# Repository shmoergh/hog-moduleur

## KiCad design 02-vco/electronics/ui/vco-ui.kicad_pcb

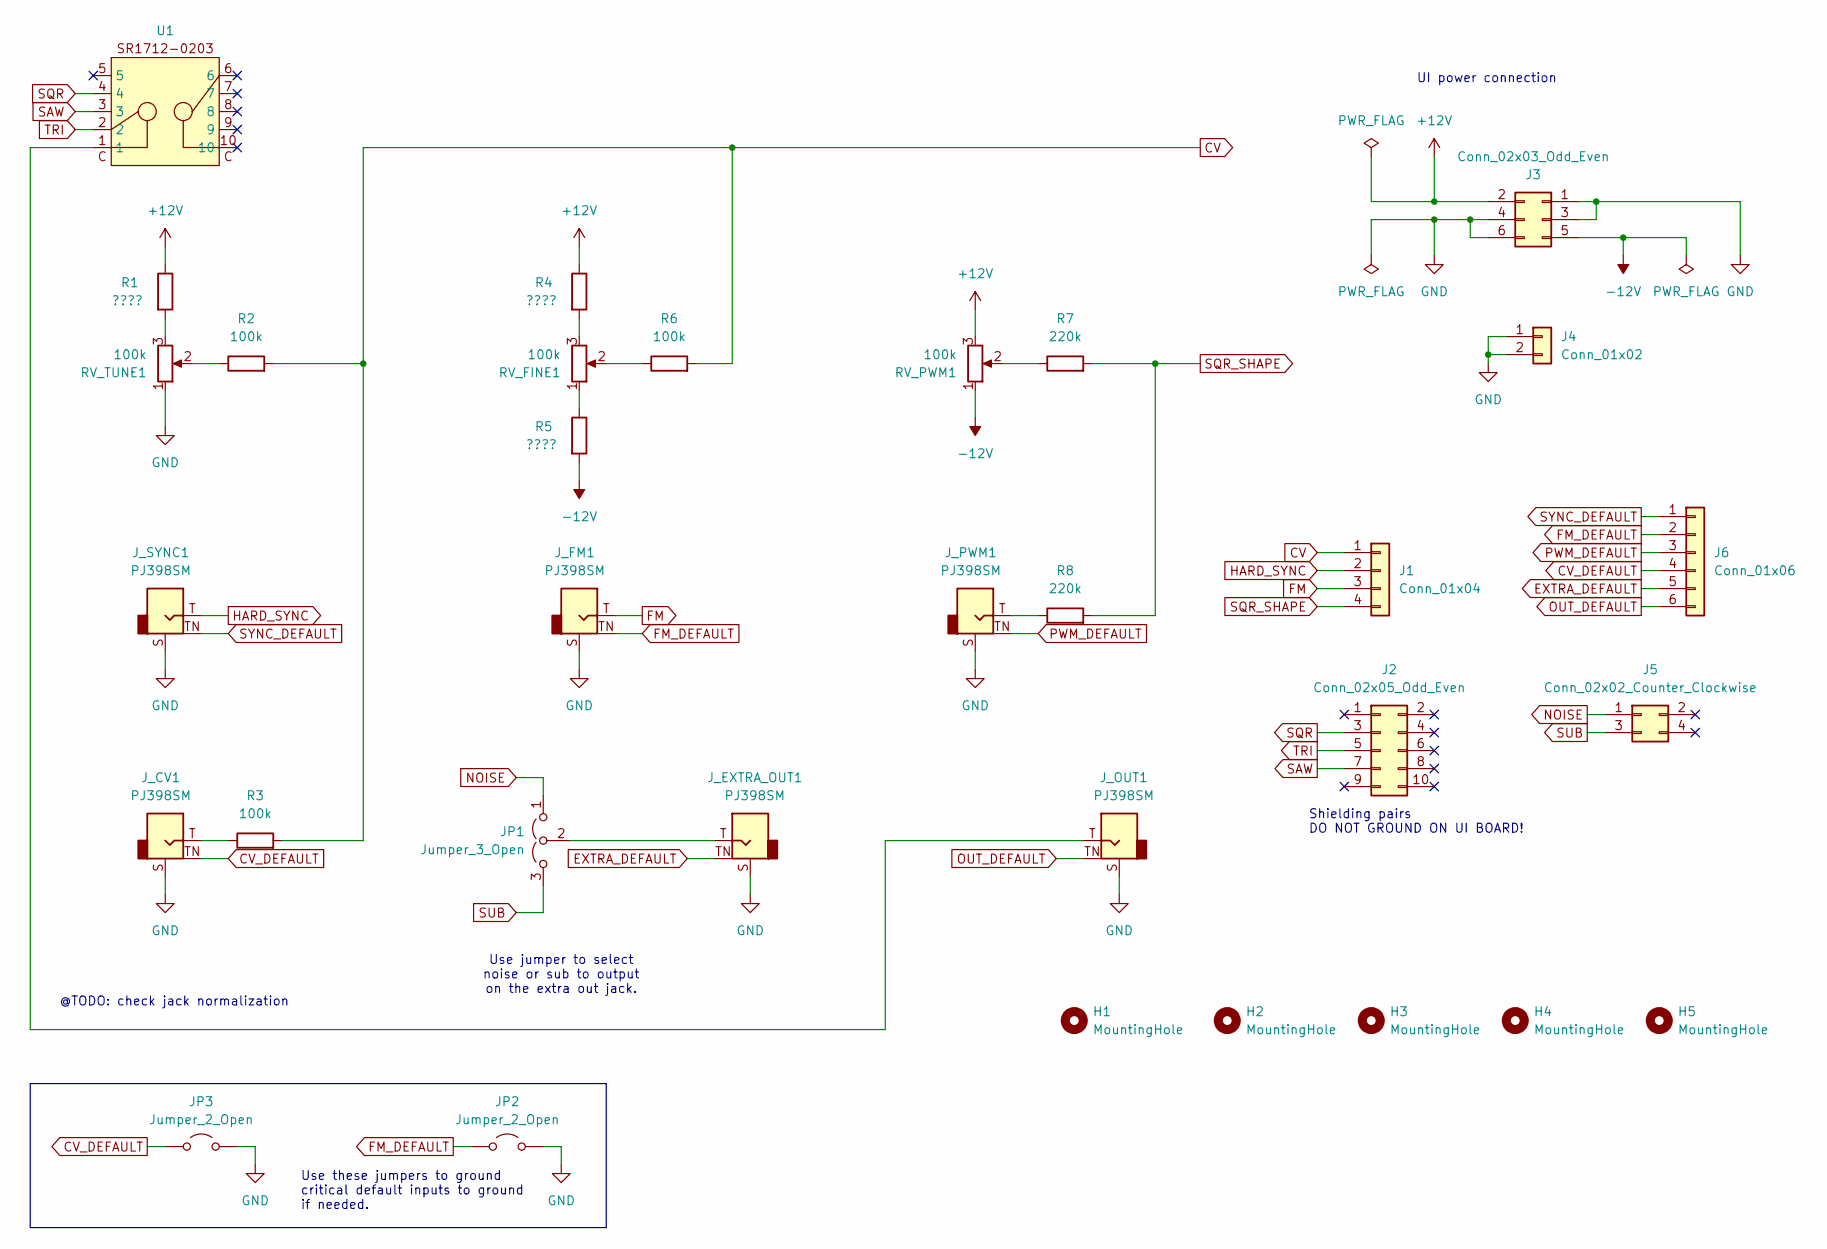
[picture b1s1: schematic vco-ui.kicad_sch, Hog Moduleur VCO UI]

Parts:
H1, H2, H3, H4, H5: MountingHole; MountingHole_3.2mm_M3_DIN965_Pad
J1: Conn_01x04; PinSocket_1x04_P2.54mm_Vertical
J2: Conn_02x05_Odd_Even; PinSocket_2x05_P2.54mm_Vertical
J3: Conn_02x03_Odd_Even; PinSocket_2x03_P2.54mm_Vertical
J4: Conn_01x02; PinSocket_1x02_P2.54mm_Vertical
J5: Conn_02x02_Counter_Clockwise; PinSocket_2x02_P2.54mm_Vertical
J6: Conn_01x06; PinSocket_1x06_P2.54mm_Vertical
JP1: Jumper_3_Open; PinHeader_1x03_P2.54mm_Horizontal
JP2, JP3: Jumper_2_Open; PinHeader_1x02_P2.54mm_Horizontal
J_CV1: PJ398SM; Jack_3.5mm_QingPu_WQP-PJ398SM_Vertical_CircularHoles
J_EXTRA_OUT1: PJ398SM; Jack_3.5mm_QingPu_WQP-PJ398SM_Vertical_CircularHoles
J_FM1: PJ398SM; Jack_3.5mm_QingPu_WQP-PJ398SM_Vertical_CircularHoles
J_OUT1: PJ398SM; Jack_3.5mm_QingPu_WQP-PJ398SM_Vertical_CircularHoles
J_PWM1: PJ398SM; Jack_3.5mm_QingPu_WQP-PJ398SM_Vertical_CircularHoles
J_SYNC1: PJ398SM; Jack_3.5mm_QingPu_WQP-PJ398SM_Vertical_CircularHoles
R1, R4, R5: ????; R_Axial_DIN0207_L6.3mm_D2.5mm_P7.62mm_Horizontal
R2, R3, R6: 100k; R_Axial_DIN0207_L6.3mm_D2.5mm_P7.62mm_Horizontal
R7, R8: 220k; R_Axial_DIN0207_L6.3mm_D2.5mm_P7.62mm_Horizontal
RV_FINE1: 100k; Potentiometer_Bourns_Single-PTV09A
RV_PWM1: 100k; Potentiometer_Bourns_Single-PTV09A
RV_TUNE1: 100k; Potentiometer_Bourns_Single-PTV09A
U1: SR1712-0203; Part No. 105-SR1712F-23NS

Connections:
+12V: J3.2, R1.1, R4.1, RV_PWM1.3
-12V: J3.5, R5.2, RV_PWM1.1
CV: J1.1, R2.2, R3.2, R6.2
CV_DEFAULT: J6.4, JP3.1 (A), J_CV1.TN
EXTRA_DEFAULT: J6.5, J_EXTRA_OUT1.TN
FM: J1.3, J_FM1.T
FM_DEFAULT: J6.2, JP2.1 (A), J_FM1.TN
GND: J3.1, J3.3, J3.4, J3.6, J4.1, J4.2, JP2.2 (B), JP3.2 (B), J_CV1.S, J_EXTRA_OUT1.S, J_FM1.S, J_OUT1.S, J_PWM1.S, J_SYNC1.S, RV_TUNE1.1
HARD_SYNC: J1.2, J_SYNC1.T
NOISE: J5.1, JP1.1 (A)
unnamed: JP1.2 (C), J_EXTRA_OUT1.T
unnamed: J_CV1.T, R3.1
unnamed: J_OUT1.T, U1.1
unnamed: J_PWM1.T, R8.1
unnamed: R1.2, RV_TUNE1.3
unnamed: R2.1, RV_TUNE1.2
unnamed: R4.2, RV_FINE1.3
unnamed: R5.1, RV_FINE1.1
unnamed: R6.1, RV_FINE1.2
unnamed: R7.1, RV_PWM1.2
OUT_DEFAULT: J6.6, J_OUT1.TN
PWM_DEFAULT: J6.3, J_PWM1.TN
SAW: J2.7, U1.3
SQR: J2.3, U1.4
SQR_SHAPE: J1.4, R7.2, R8.2
SUB: J5.3, JP1.3 (B)
SYNC_DEFAULT: J6.1, J_SYNC1.TN
TRI: J2.5, U1.2

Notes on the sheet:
@TODO: check jack normalization
Use these jumpers to ground critical default inputs to ground if needed.
UI power connection
Use jumper to select noise or sub to output on the extra out jack.
Shielding pairs DO NOT GROUND ON UI BOARD!

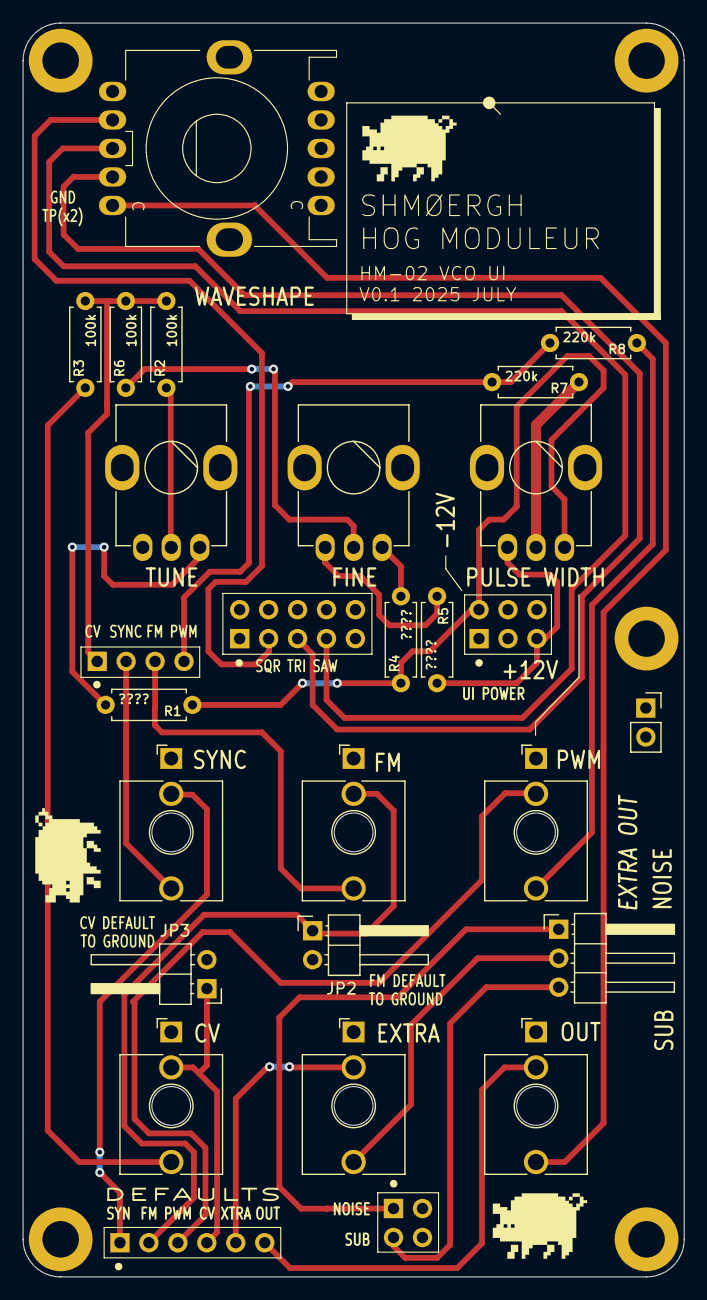
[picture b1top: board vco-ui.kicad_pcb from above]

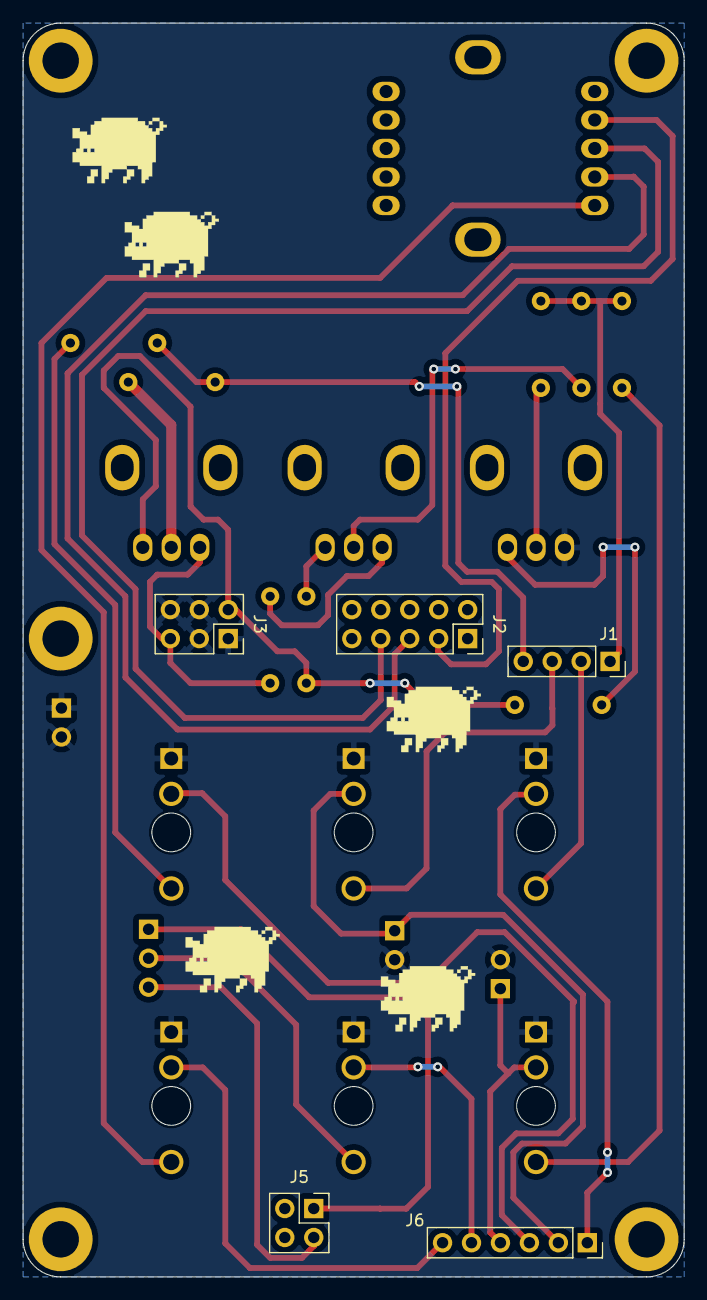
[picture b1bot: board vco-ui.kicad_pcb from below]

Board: 2 copper layers, 58.0 x 110.0 mm, 32 parts (5 on the bottom side), 28 nets.

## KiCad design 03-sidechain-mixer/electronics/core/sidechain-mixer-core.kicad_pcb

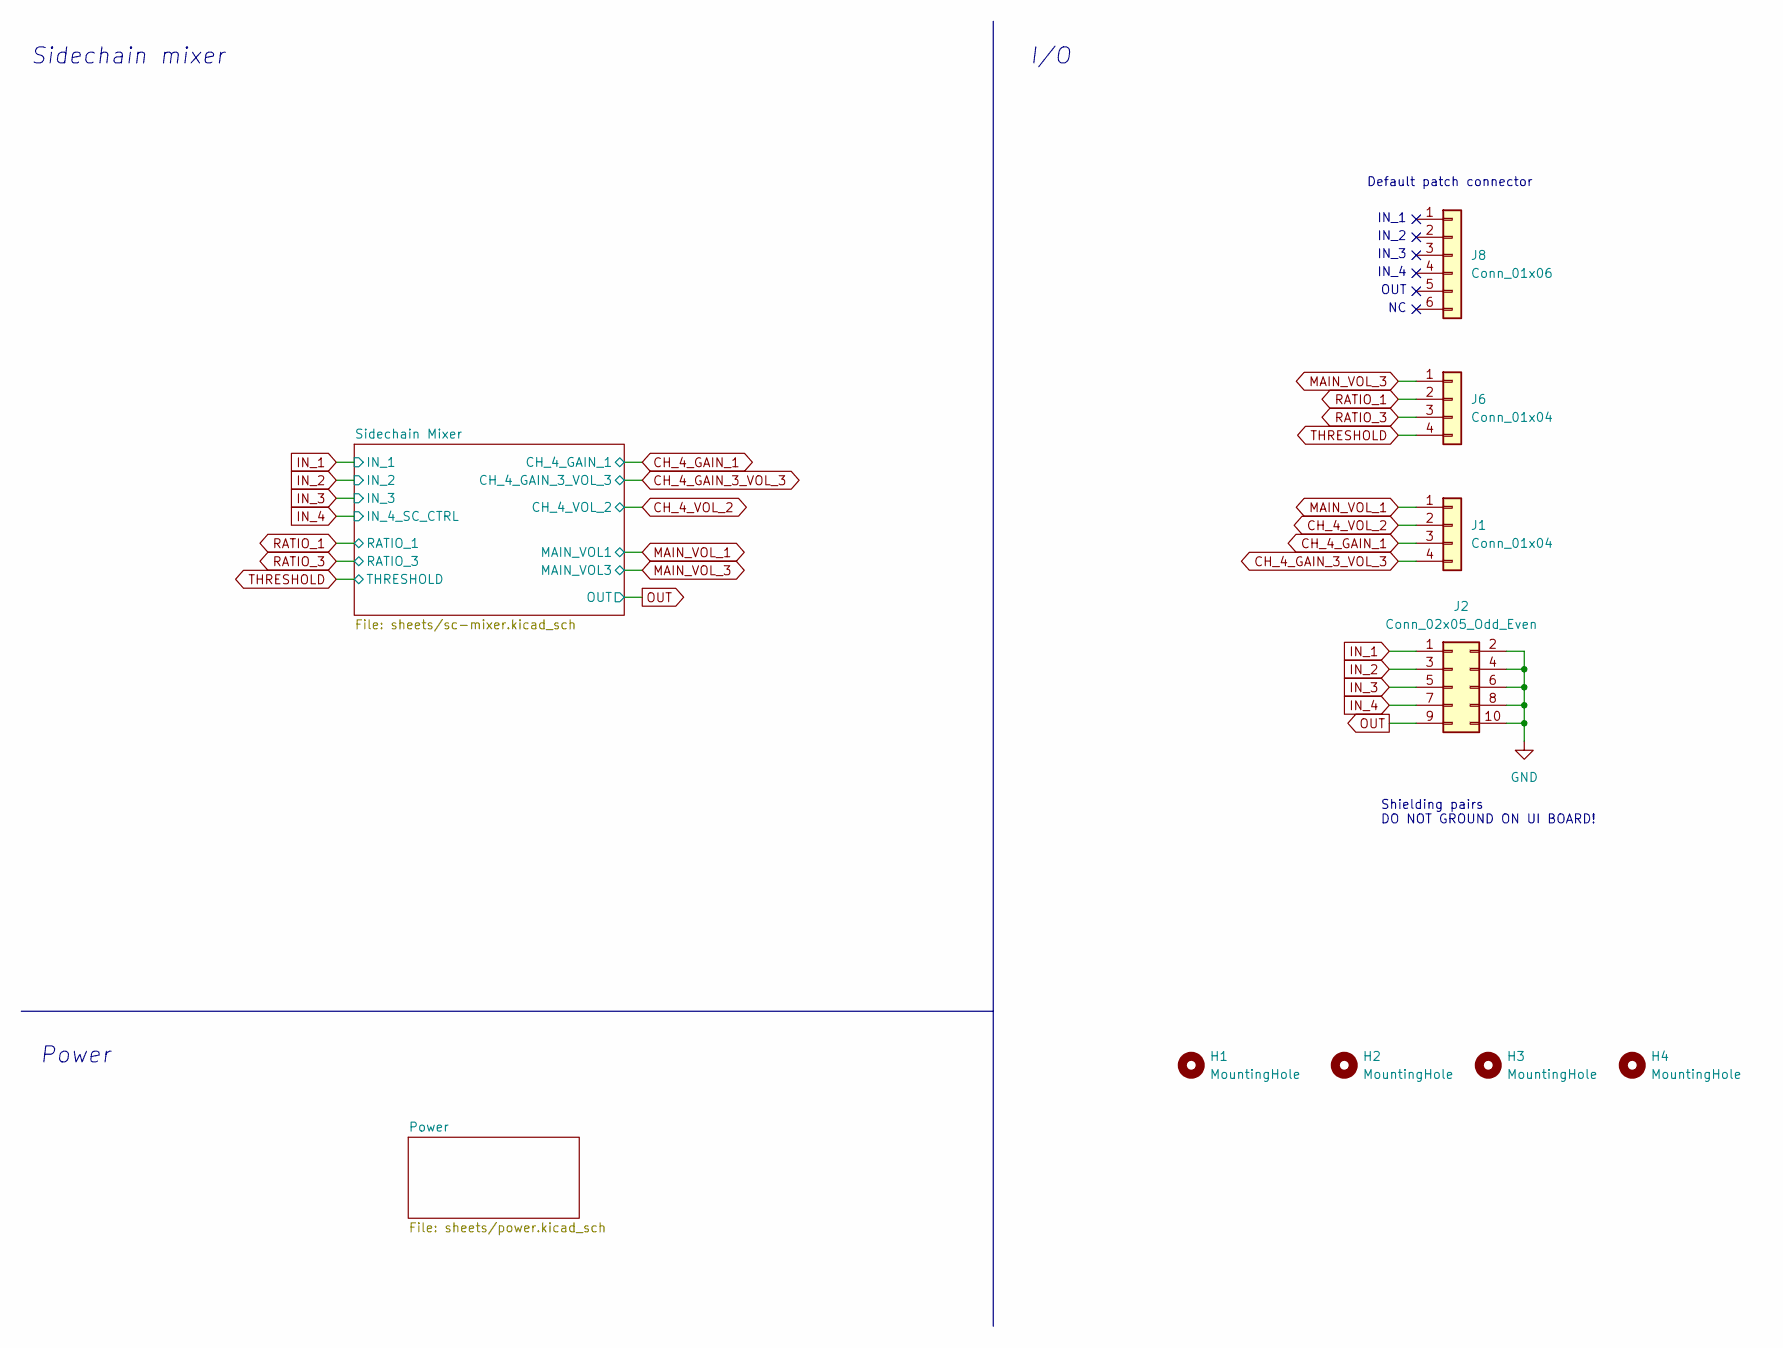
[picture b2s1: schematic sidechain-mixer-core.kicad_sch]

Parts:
H1, H2, H3, H4: MountingHole; MountingHole_3.2mm_M3_DIN965_Pad
J1, J6: Conn_01x04; PinHeader_1x04_P2.54mm_Vertical
J2: Conn_02x05_Odd_Even; PinHeader_2x05_P2.54mm_Vertical; Mouser Part no. 200-TSW10507TD
J8: Conn_01x06; PinHeader_1x06_P2.54mm_Vertical; Mouser Part no. 474-PRT-09280

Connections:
CH_4_GAIN_1: J1.3; also elsewhere on the board
CH_4_GAIN_3_VOL_3: J1.4; also elsewhere on the board
CH_4_VOL_2: J1.2; also elsewhere on the board
IN_1: J2.1; also elsewhere on the board
IN_2: J2.3; also elsewhere on the board
IN_3: J2.5; also elsewhere on the board
IN_4: J2.7; also elsewhere on the board
MAIN_VOL_1: J1.1; also elsewhere on the board
MAIN_VOL_3: J6.1; also elsewhere on the board
OUT: J2.9; also elsewhere on the board
RATIO_1: J6.2; also elsewhere on the board
RATIO_3: J6.3; also elsewhere on the board
THRESHOLD: J6.4; also elsewhere on the board

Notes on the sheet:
Power
IN_3
Default patch connector
IN_1
Shielding pairs DO NOT GROUND ON UI BOARD!
OUT
Sidechain mixer
IN_2
I/O
IN_4

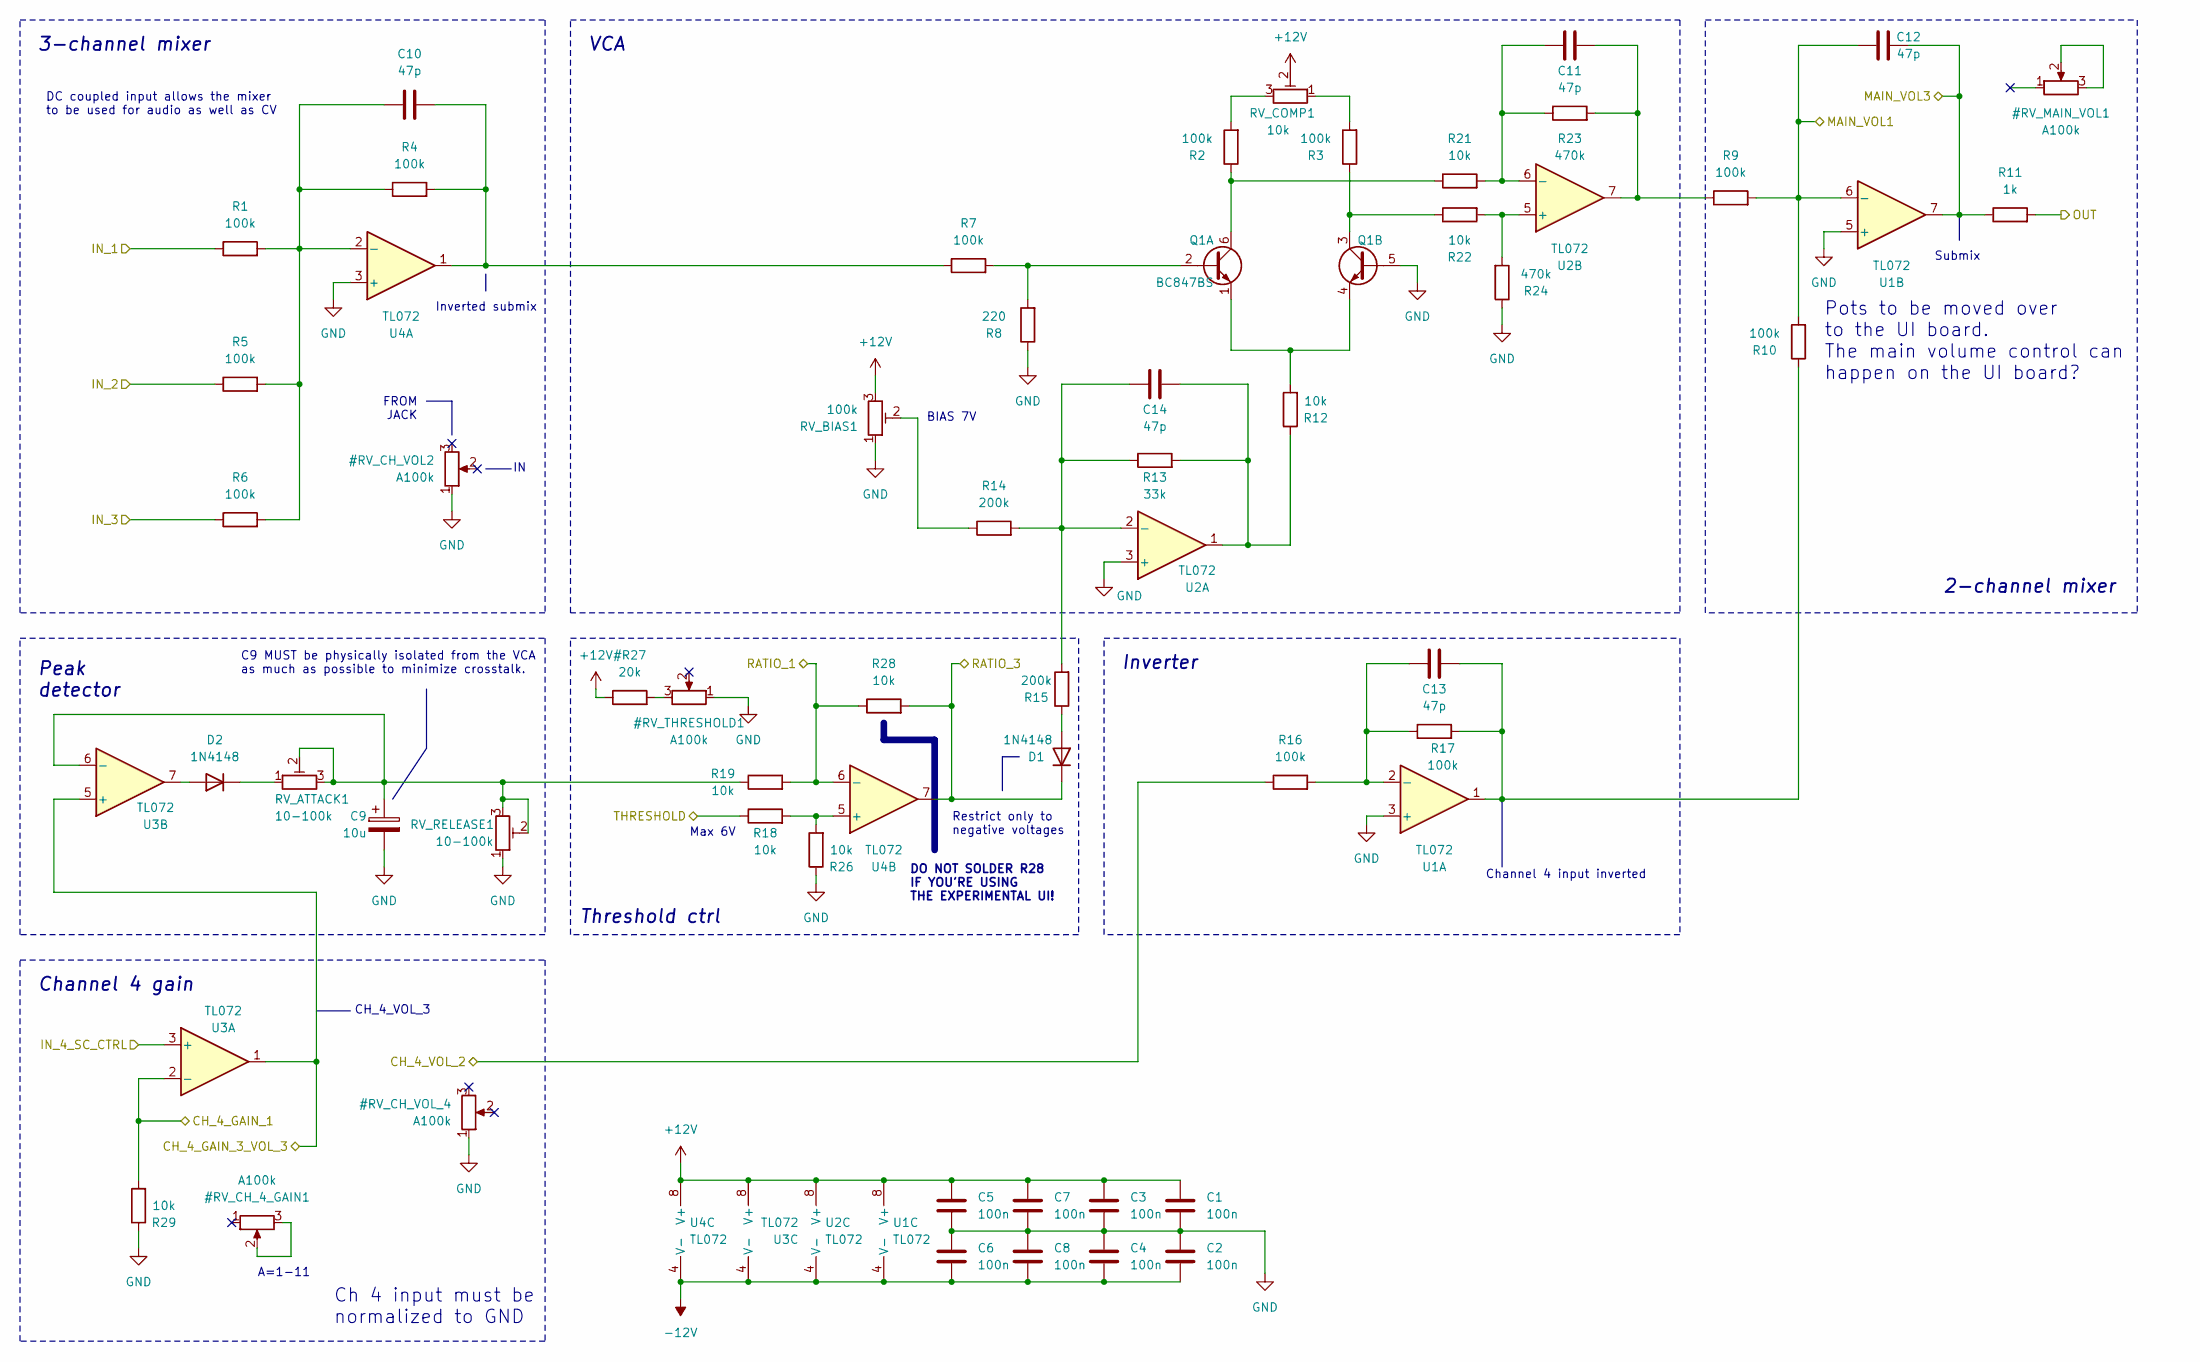
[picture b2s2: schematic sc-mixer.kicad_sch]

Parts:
C1, C2, C3, C4, C5, C6, C7, C8: 100n; C_0603_1608Metric; LCSC C14663
C9: 10u; CP_Elec_4x5.4; LCSC C72485
C10, C11, C12, C13, C14: 47p; C_0603_1608Metric_Pad1.08x0.95mm_HandSolder; LCSC C1671
D1, D2: 1N4148; D_SOD-123; LCSC C81598
Q1: BC847BS; SOT-363_SC-70-6; LCSC C5380687
R1, R2, R3, R4, R5, R6, R7, R9, R10, R16, R17: 100k; R_0603_1608Metric; LCSC C25803
R8: 220; R_0603_1608Metric; LCSC C22962
R11: 1k; R_0603_1608Metric; LCSC C21190
R12, R21, R22: 10k; R_0603_1608Metric; LCSC C25804
R13: 33k; R_0603_1608Metric; LCSC C4216
R14, R15: 200k; R_0603_1608Metric; LCSC C25811
R18, R19, R26, R28, R29: 10k; R_Axial_DIN0207_L6.3mm_D2.5mm_P7.62mm_Horizontal
R23, R24: 470k; R_0603_1608Metric; LCSC C23178
RV_ATTACK1: 10-100k; Potentiometer_ACP_CA6-H2,5_Horizontal
RV_BIAS1: 100k; Potentiometer_ACP_CA6-H2,5_Horizontal
RV_COMP1: 10k; Potentiometer_ACP_CA6-H2,5_Horizontal
RV_RELEASE1: 10-100k; Potentiometer_ACP_CA6-H2,5_Horizontal
U1, U2, U3, U4: TL072; SOIC-8_3.9x4.9mm_P1.27mm; LCSC C6961

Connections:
-12V: C2.2, C4.2, C6.2, C8.2, U1.4 (V-), U2.4 (V-), U3.4 (V-), U4.4 (V-); also elsewhere on the board
CH_4_GAIN_1: R29.2, U3.2 (-); also elsewhere on the board
CH_4_GAIN_3_VOL_3: U3.1, U3.5 (+); also elsewhere on the board
CH_4_VOL_2: R16.1; also elsewhere on the board
IN_1: R1.1; also elsewhere on the board
IN_2: R5.1; also elsewhere on the board
IN_3: R6.1; also elsewhere on the board
IN_4: U3.3 (+); also elsewhere on the board
MAIN_VOL_1: C12.1, R9.2, R10.2, U1.6 (-); also elsewhere on the board
MAIN_VOL_3: C12.2, R11.1, U1.7; also elsewhere on the board
unnamed: C10.2, R4.2, R7.1, U4.1
unnamed: C11.2, R9.1, R23.2, U2.7
unnamed: C13.2, R10.1, R17.2, U1.1
unnamed: C14.2, R12.1, R13.2, U2.1
unnamed: D1.2 (A), R15.1
unnamed: D2.2 (A), U3.7
unnamed: D2.1 (K), RV_ATTACK1.1
unnamed: Q1.2 (B1), R7.2, R8.2
unnamed: Q1.6 (C1), R2.1, R21.1
unnamed: Q1.1 (E1), Q1.4 (E2), R12.2
unnamed: Q1.3 (C2), R3.1, R22.1
unnamed: R2.2, RV_COMP1.3
unnamed: R3.2, RV_COMP1.1
unnamed: R14.1, RV_BIAS1.2
unnamed: C13.1, R16.2, R17.1, U1.2 (-)
unnamed: C14.1, R13.1, R14.2, R15.2, U2.2 (-)
unnamed: R22.2, R24.2, U2.5 (+)
unnamed: C11.1, R21.2, R23.1, U2.6 (-)
unnamed: C9.1, R19.1, RV_ATTACK1.2, RV_ATTACK1.3, RV_RELEASE1.2, RV_RELEASE1.3, U3.6 (-)
unnamed: C10.1, R1.2, R4.1, R5.2, R6.2, U4.2 (-)
unnamed: R18.2, R26.2, U4.5 (+)
OUT: R11.2; also elsewhere on the board
RATIO_1: R19.2, R28.1, U4.6 (-); also elsewhere on the board
RATIO_3: D1.1 (K), R28.2, U4.7; also elsewhere on the board
THRESHOLD: R18.1; also elsewhere on the board

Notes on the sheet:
2-channel mixer
Channel 4 gain
FROM JACK
A=1-11
Pots to be moved over to the UI board. The main volume control can happen on the UI board?
DO NOT SOLDER R28 IF YOU'RE USING THE EXPERIMENTAL UI!
Inverter
Submix
VCA
BIAS 7V
Channel 4 input inverted
Max 6V
Ch 4 input must be normalized to GND
3-channel mixer
Restrict only to negative voltages
DC coupled input allows the mixer to be used for audio as well as CV
C9 MUST be physically isolated from the VCA as much as possible to minimize crosstalk.
CH_4_VOL_3
Peak detector
Threshold ctrl
Inverted submix

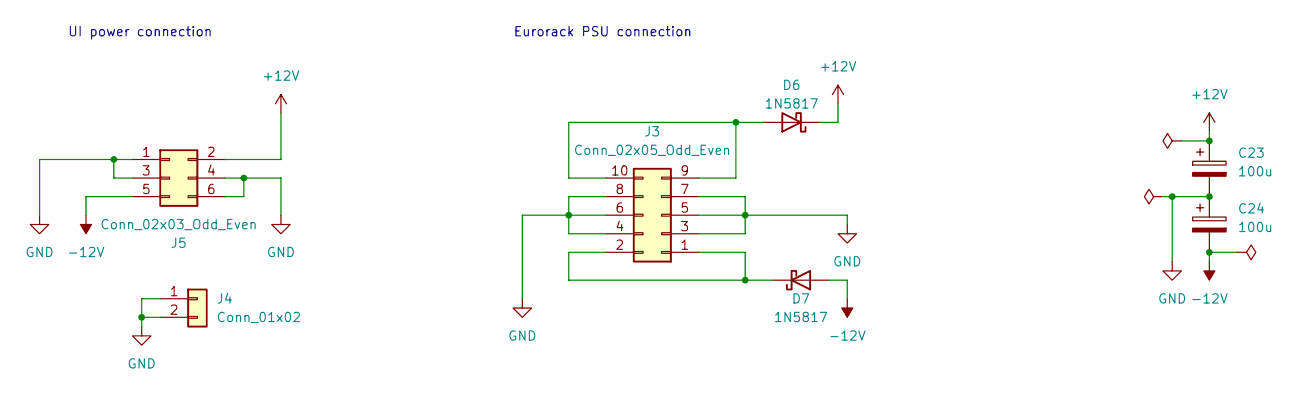
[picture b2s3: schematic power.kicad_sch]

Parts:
C23, C24: 100u; CP_Elec_6.3x7.7; LCSC C2836437
D6, D7: 1N5817; D_SOD-323; LCSC C5190152
J3: Conn_02x05_Odd_Even; IDC-Header_2x05_P2.54mm_Horizontal
J4: Conn_01x02; PinHeader_1x02_P2.54mm_Vertical
J5: Conn_02x03_Odd_Even; PinHeader_2x03_P2.54mm_Vertical

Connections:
-12V: C24.2, D7.2 (A), J5.5; also elsewhere on the board
unnamed: D6.2 (A), J3.9, J3.10
unnamed: D7.1 (K), J3.1, J3.2

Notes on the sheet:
UI power connection
Eurorack PSU connection

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
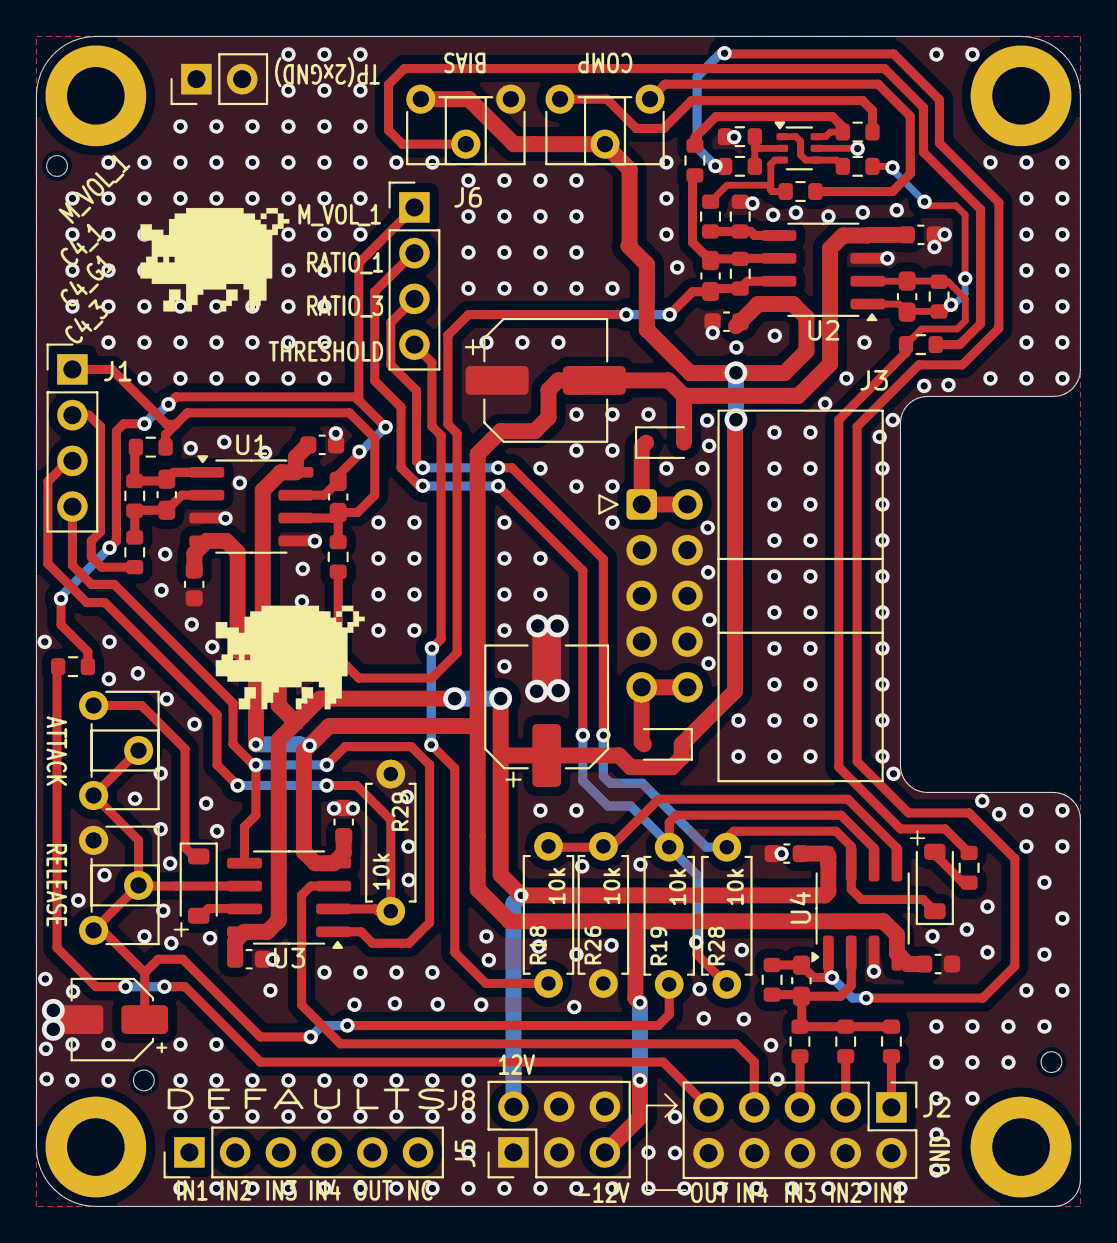
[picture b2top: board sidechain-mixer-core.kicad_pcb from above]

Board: 2 copper layers, 58.0 x 65.0 mm, 66 parts (0 on the bottom side), 39 nets.

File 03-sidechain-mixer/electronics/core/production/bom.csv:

Designator,Footprint,Quantity,Value,LCSC Part #
"C1, C2, C3, C4, C5, C6, C7, C8",0603,8,100n,C14663
"C10, C11, C12, C13, C14",0603,5,47p,C1671
"C23, C24",CP_Elec_6.3x7.7,2,100u,C2836437
C9,CP_Elec_4x5.4,1,10u,C72485
"D1, D2",D_SOD-123,2,1N4148,C81598
"D6, D7",D_SOD-323,2,1N5817,C5190152
"J1, J6",PinHeader_1x04_P2.54mm_Vertical,2,Conn_01x04,
J2,PinHeader_2x05_P2.54mm_Vertical,1,Conn_02x05_Odd_Even,
J3,IDC-Header_2x05_P2.54mm_Horizontal,1,Conn_02x05_Odd_Even,
J4,PinHeader_1x02_P2.54mm_Vertical,1,Conn_01x02,
J5,PinHeader_2x03_P2.54mm_Vertical,1,Conn_02x03_Odd_Even,
J8,PinHeader_1x06_P2.54mm_Vertical,1,Conn_01x06,
Q1,SOT-363_SC-70-6,1,BC847BS,C5380687
"R1, R10, R16, R17, R2, R3, R4, R5, R6, R7, R9",0603,11,100k,C25803
R11,0603,1,1k,C21190
"R12, R21, R22",0603,3,10k,C25804
R13,0603,1,33k,C4216
"R14, R15",0603,2,200k,C25811
"R18, R19, R26, R28, R29",R_Axial_DIN0207_L6.3mm_D2.5mm_P7.62mm_Horizontal,5,10k,
"R23, R24",0603,2,470k,C23178
R8,0603,1,220,C22962
"RV_ATTACK1, RV_RELEASE1","Potentiometer_ACP_CA6-H2,5_Horizontal",2,10-100k,
RV_BIAS1,"Potentiometer_ACP_CA6-H2,5_Horizontal",1,100k,
RV_COMP1,"Potentiometer_ACP_CA6-H2,5_Horizontal",1,10k,
"U1, U2, U3, U4",SOIC-8_3.9x4.9mm_P1.27mm,4,TL072,C6961

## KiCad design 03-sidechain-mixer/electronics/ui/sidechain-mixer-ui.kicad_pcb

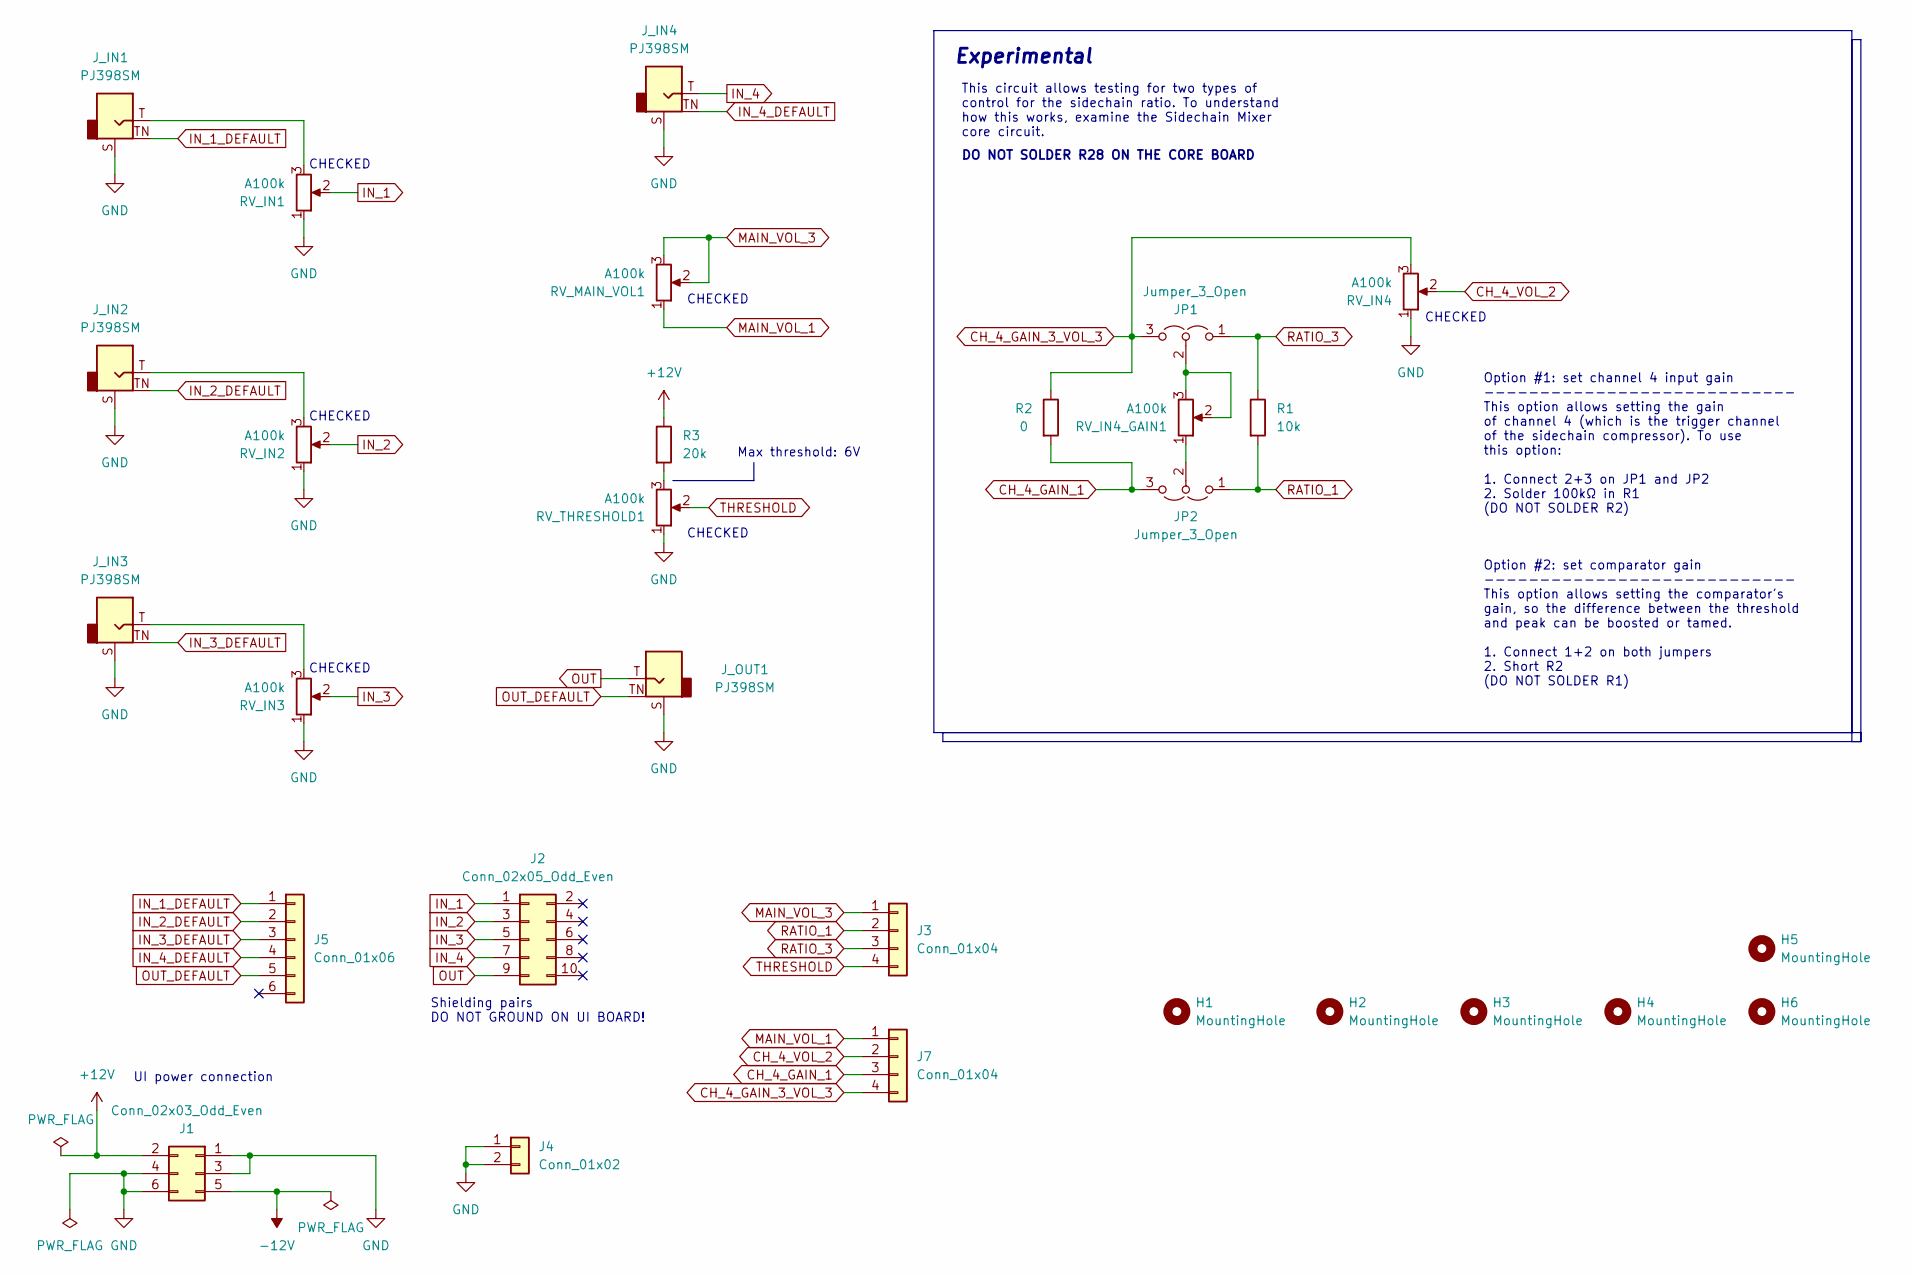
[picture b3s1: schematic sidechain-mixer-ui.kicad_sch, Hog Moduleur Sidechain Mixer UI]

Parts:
H1, H2, H3, H4, H5, H6: MountingHole; MountingHole_3.2mm_M3_DIN965_Pad
J1: Conn_02x03_Odd_Even; PinSocket_2x03_P2.54mm_Vertical; Part no. 200-SSW10301TD
J2: Conn_02x05_Odd_Even; PinSocket_2x05_P2.54mm_Vertical
J3, J7: Conn_01x04; PinHeader_1x04_P2.54mm_Vertical
J4: Conn_01x02; PinSocket_1x02_P2.54mm_Vertical; Part no. 200-SSW10201TS
J5: Conn_01x06; PinSocket_1x06_P2.54mm_Vertical; Part no. 200-SSW10601TS
JP1, JP2: Jumper_3_Open; PinHeader_1x03_P2.54mm_Vertical
J_IN1, J_IN2, J_IN3, J_IN4: PJ398SM; Jack_3.5mm_QingPu_WQP-PJ398SM_Vertical_CircularHoles; Part no. PJ398SM
J_OUT1: PJ398SM; Jack_3.5mm_QingPu_WQP-PJ398SM_Vertical_CircularHoles; Part no. PJ398SM
R1: 10k; R_Axial_DIN0207_L6.3mm_D2.5mm_P7.62mm_Horizontal
R2: 0; R_Axial_DIN0207_L6.3mm_D2.5mm_P7.62mm_Horizontal
R3: 20k; R_Axial_DIN0207_L6.3mm_D2.5mm_P7.62mm_Horizontal
RV_IN1, RV_IN2, RV_IN3: A100k; TRIM_PTA3043-2010CIA503; Part no. 652-PTA30432015A104
RV_IN4, RV_IN4_GAIN1: A100k; Potentiometer_Bourns_Single-PTV09A; Part no. 652-PTV09A4025FB104
RV_MAIN_VOL1: A100k; Potentiometer_Bourns_Single-PTV09A; Part no. 652-PTV09A4025FB104
RV_THRESHOLD1: A100k; Potentiometer_Bourns_Single-PTV09A; Part no. 652-PTV09A4025FB104

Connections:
+12V: J1.2, R3.1
-12V: J1.5
CH_4_GAIN_1: J7.3, JP2.3 (B), R2.2
CH_4_GAIN_3_VOL_3: J7.4, JP1.3 (B), R2.1, RV_IN4.3
CH_4_VOL_2: J7.2, RV_IN4.2
GND: J1.1, J1.3, J1.4, J1.6, J4.1, J4.2, J_IN1.S, J_IN2.S, J_IN3.S, J_IN4.S, J_OUT1.S, RV_IN1.1, RV_IN2.1, RV_IN3.1, RV_IN4.1, RV_THRESHOLD1.1
IN_1: J2.1, RV_IN1.2
IN_1_DEFAULT: J5.1, J_IN1.TN
IN_2: J2.3, RV_IN2.2
IN_2_DEFAULT: J5.2, J_IN2.TN
IN_3: J2.5, RV_IN3.2
IN_3_DEFAULT: J5.3, J_IN3.TN
IN_4: J2.7, J_IN4.T
IN_4_DEFAULT: J5.4, J_IN4.TN
MAIN_VOL_1: J7.1, RV_MAIN_VOL1.1
MAIN_VOL_3: J3.1, RV_MAIN_VOL1.2, RV_MAIN_VOL1.3
unnamed: JP1.2 (C), RV_IN4_GAIN1.2, RV_IN4_GAIN1.3
unnamed: JP2.2 (C), RV_IN4_GAIN1.1
unnamed: J_IN1.T, RV_IN1.3
unnamed: J_IN2.T, RV_IN2.3
unnamed: J_IN3.T, RV_IN3.3
unnamed: R3.2, RV_THRESHOLD1.3
OUT: J2.9, J_OUT1.T
OUT_DEFAULT: J5.5, J_OUT1.TN
RATIO_1: J3.2, JP2.1 (A), R1.2
RATIO_3: J3.3, JP1.1 (A), R1.1
THRESHOLD: J3.4, RV_THRESHOLD1.2

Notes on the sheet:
Option #2: set comparator gain ---------------------------- This option allows setting the comparator's gain, so the difference between the threshold and peak can be boosted or tamed. 1. Connect 1+2 on both jumpers 2. Short R2 (DO NOT SOLDER R1)
Max threshold: 6V
CHECKED
This circuit allows testing for two types of control for the sidechain ratio. To understand how this works, examine the Sidechain Mixer core circuit.
UI power connection
Option #1: set channel 4 input gain ---------------------------- This option allows setting the gain of channel 4 (which is the trigger channel of the sidechain compressor). To use this option: 1. Connect 2+3 on JP1 and JP2 2. Solder 100kΩ in R1 (DO NOT SOLDER R2)
DO NOT SOLDER R28 ON THE CORE BOARD
Experimental
Shielding pairs DO NOT GROUND ON UI BOARD!

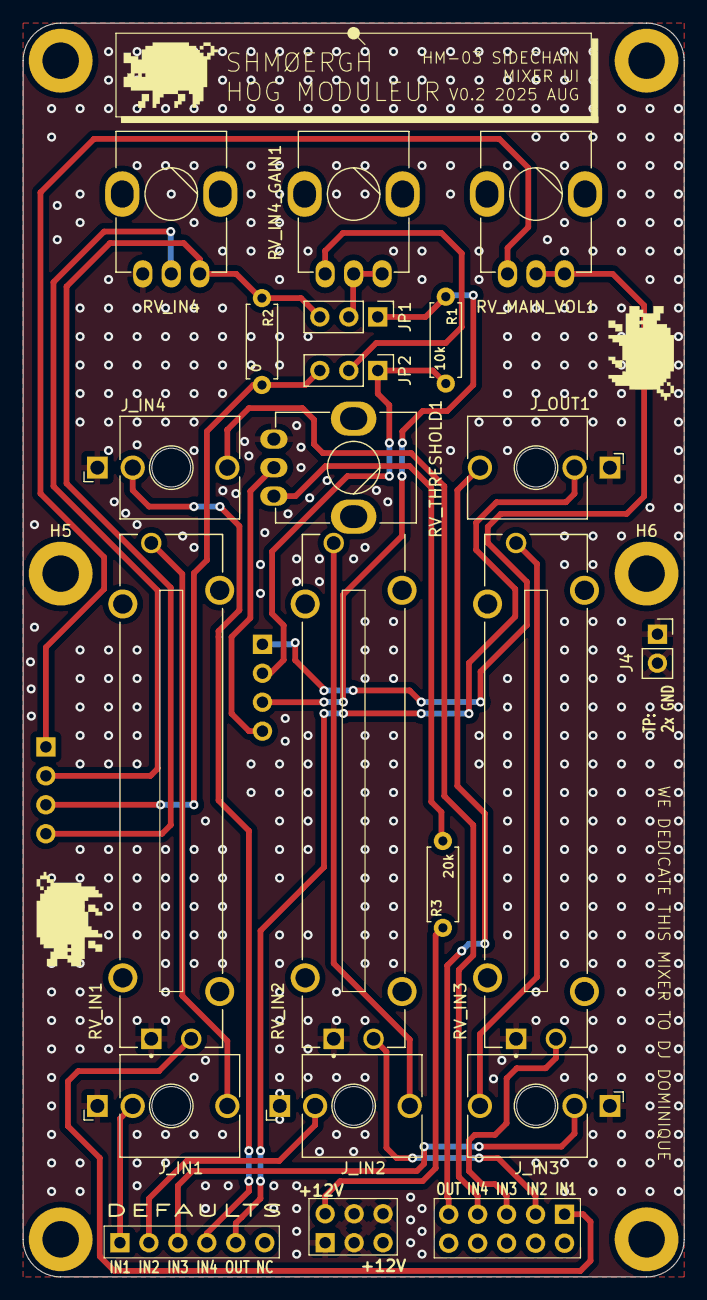
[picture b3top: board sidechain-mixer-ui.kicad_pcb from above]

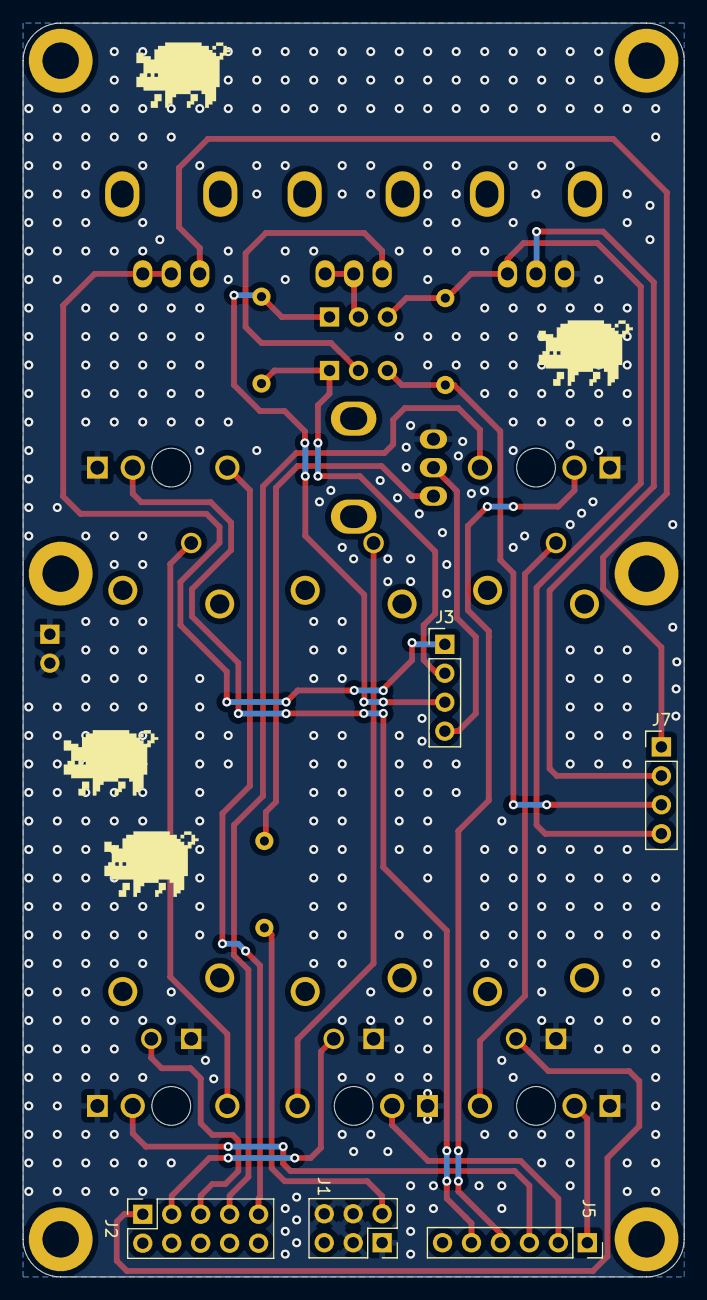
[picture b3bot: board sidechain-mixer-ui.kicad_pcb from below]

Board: 2 copper layers, 58.0 x 110.0 mm, 29 parts (5 on the bottom side), 26 nets.

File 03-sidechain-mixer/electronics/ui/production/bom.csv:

Designator,Footprint,Quantity,Value,LCSC Part #
J1,PinSocket_2x03_P2.54mm_Vertical,1,Conn_02x03_Odd_Even,
J2,PinSocket_2x05_P2.54mm_Vertical,1,Conn_02x05_Odd_Even,
"J3, J7",PinHeader_1x04_P2.54mm_Vertical,2,Conn_01x04,
J4,PinSocket_1x02_P2.54mm_Vertical,1,Conn_01x02,
J5,PinSocket_1x06_P2.54mm_Vertical,1,Conn_01x06,
"J_IN1, J_IN2, J_IN3, J_IN4, J_OUT1",Jack_3.5mm_QingPu_WQP-PJ398SM_Vertical_CircularHoles,5,PJ398SM,
R1,R_Axial_DIN0207_L6.3mm_D2.5mm_P7.62mm_Horizontal,1,10k,
R2,R_Axial_DIN0207_L6.3mm_D2.5mm_P7.62mm_Horizontal,1,0,
R3,R_Axial_DIN0207_L6.3mm_D2.5mm_P7.62mm_Horizontal,1,20k,
"RV_IN1, RV_IN2, RV_IN3",TRIM_PTA3043-2010CIA503,3,A100k,
"RV_IN4, RV_IN4_GAIN1, RV_MAIN_VOL1, RV_THRESHOLD1",Potentiometer_Bourns_Single-PTV09A,4,A100k,
